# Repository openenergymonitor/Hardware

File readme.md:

## OpenEnergyMonitor Hardware

OpenEnergyMonitor hardware is open source hardware. This github repository hosts all the Eagle schematic and board files for the hardware units in addition to images for quick access.

**Update: most hardware designs have now been moved to dedicated repos, see individual folders**

### EmonTx

- [emonTx SMT V3](emonTxV3) - Latest generation of the emonTx Arduino compatible low power wireless energy monitoring node
- [emonTx Through-hole V2](emonTxV2) - A low-power wireless energy-monitoring node - Arduino compatible

### EmonTx Shield

- [emonTx Shield SMT](emontx-shield-smt) - An Arduino compatible energy monitoring shield
- [emonTx Shield Through-hole](emontx-shield-v1) - A wireless energy monitoring Arduino compatible shield

### EmonTH

- [emonTH](emonTH) - Temperature and humidity monitoring node

### EmonGLCD

- [emonGLCD](emonGLCD_V1) - Wireless open-source graphical LCD display unit - Arduino compatible

### RF12Pi Adapter Board

- [RF12Pi Adapter Board](RFM2Pi/readme.md)

### Development

- [12 Input Pulse Counter](12-input-pulse-counter) - Design in development for a 12-input puse counter for interfacing with 12 utility meters. 12 Input Pulse counter development notes and documentation can be found on the main OpenEnergyMonitor site [here](http://openenergymonitor.org/emon/buildingblocks/12-input-pulse-counting)

- [In-line energy monitor + Relay unit](relay-unit/readme.md)

### Open Hardware

Hardware designs (schematics and CAD) files are licensed under the [Creative Commons Attribution-ShareAlike 3.0 Unported License](http://creativecommons.org/licenses/by-sa/3.0/) and follow the terms of the [OSHW (Open-source hardware) Statement of Principles 1.0.](http://freedomdefined.org/OSHW)

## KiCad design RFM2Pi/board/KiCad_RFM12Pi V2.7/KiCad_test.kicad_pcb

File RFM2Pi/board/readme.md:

## moved to https://github.com/openenergymonitor/RFM2Pi

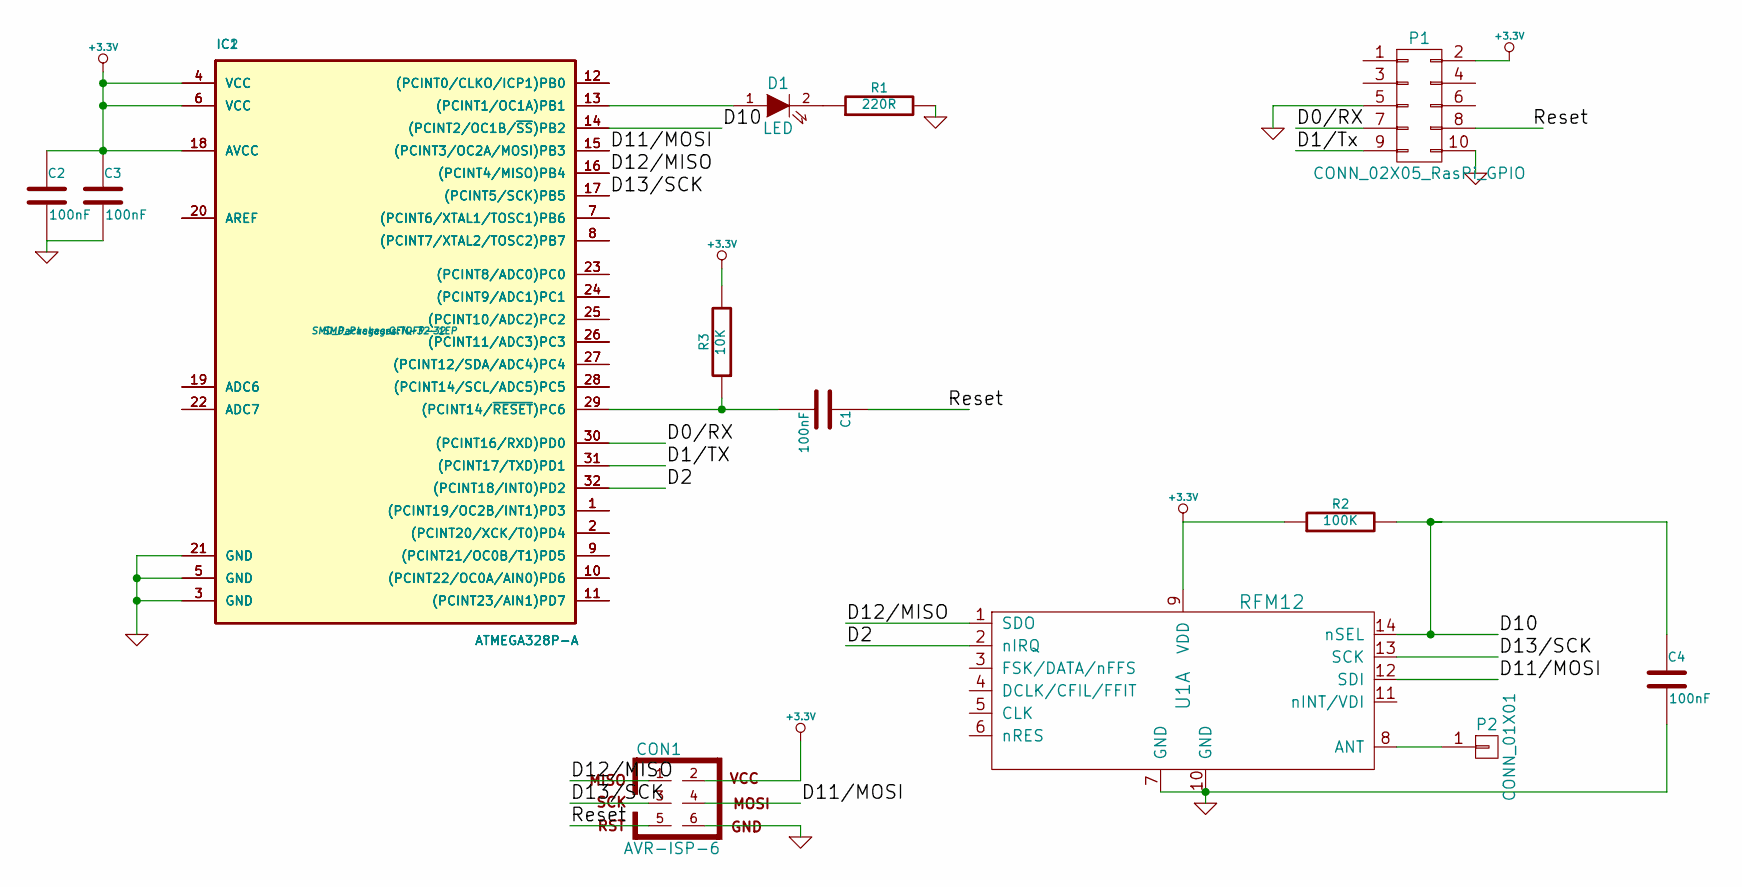
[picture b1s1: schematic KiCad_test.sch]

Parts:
C1, C2, C3, C4: 100nF; SMD-0603_c
CON1: AVR-ISP-6; Pin_Header_Straight_2x03
D1: LED; LED-0603
IC1: ATMEGA328P-A; TQFP-32
IC2: ATMEGA328P-A; QFN-32-1EP
P1: CONN_02X05_RasPi_GPIO; Pin_Header_Straight_2x05
P2: CONN_01X01; PINTST
R1: 220R; SMD-0603
R2: 100K; SMD-0603
R3: 10K; SMD-0603
U1: RFM12

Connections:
+3.3V: C2.1, C3.1, CON1.2, IC1.4 (VCC), IC1.6 (VCC), IC1.18 (AVCC), IC2.4 (VCC), IC2.6 (VCC), IC2.18 (AVCC), P1.2, R2.1, R3.2, U1.9 (VDD)
/D0/RX: IC1.30 ((PCINT16/RXD)PD0), IC2.30 ((PCINT16/RXD)PD0), P1.7
/D1/TX: IC1.31 ((PCINT17/TXD)PD1), IC2.31 ((PCINT17/TXD)PD1), P1.9
/D2: IC1.32 ((PCINT18/INT0)PD2), IC2.32 ((PCINT18/INT0)PD2), U1.2 (nIRQ)
/D10: C4.1, IC1.14 ((PCINT2/OC1B/~SS~)PB2), IC2.14 ((PCINT2/OC1B/~SS~)PB2), R2.2, U1.14 (nSEL)
/D11/MOSI: CON1.4, IC1.15 ((PCINT3/OC2A/MOSI)PB3), IC2.15 ((PCINT3/OC2A/MOSI)PB3), U1.12 (SDI)
/D12/MISO: CON1.1, IC1.16 ((PCINT4/MISO)PB4), IC2.16 ((PCINT4/MISO)PB4), U1.1 (SDO)
/D13/SCK: CON1.3, IC1.17 ((PCINT5/SCK)PB5), IC2.17 ((PCINT5/SCK)PB5), U1.13 (SCK)
/Reset: C1.1, CON1.5, P1.8
GND: C2.2, C3.2, C4.2, CON1.6, IC1.3 (GND), IC1.5 (GND), IC1.21 (GND), IC2.3 (GND), IC2.5 (GND), IC2.21 (GND), P1.5, P1.10, R1.2, U1.7 (GND), U1.10 (GND)
unnamed: C1.2, IC1.29 ((PCINT14/~RESET~)PC6), IC2.29 ((PCINT14/~RESET~)PC6), R3.1
unnamed: D1.1 (A), IC1.13 ((PCINT1/OC1A)PB1), IC2.13 ((PCINT1/OC1A)PB1)
unnamed: D1.2 (K), R1.1
unnamed: IC1.1 ((PCINT19/OC2B/INT1)PD3), IC2.1 ((PCINT19/OC2B/INT1)PD3)
unnamed: IC1.2 ((PCINT20/XCK/T0)PD4), IC2.2 ((PCINT20/XCK/T0)PD4)
unnamed: IC1.7 ((PCINT6/XTAL1/TOSC1)PB6), IC2.7 ((PCINT6/XTAL1/TOSC1)PB6)
unnamed: IC1.8 ((PCINT7/XTAL2/TOSC2)PB7), IC2.8 ((PCINT7/XTAL2/TOSC2)PB7)
unnamed: IC1.9 ((PCINT21/OC0B/T1)PD5), IC2.9 ((PCINT21/OC0B/T1)PD5)
unnamed: IC1.10 ((PCINT22/OC0A/AIN0)PD6), IC2.10 ((PCINT22/OC0A/AIN0)PD6)
unnamed: IC1.11 ((PCINT23/AIN1)PD7), IC2.11 ((PCINT23/AIN1)PD7)
unnamed: IC1.12 ((PCINT0/CLKO/ICP1)PB0), IC2.12 ((PCINT0/CLKO/ICP1)PB0)
unnamed: IC1.19 (ADC6), IC2.19 (ADC6)
unnamed: IC1.20 (AREF), IC2.20 (AREF)
unnamed: IC1.22 (ADC7), IC2.22 (ADC7)
unnamed: IC1.23 ((PCINT8/ADC0)PC0), IC2.23 ((PCINT8/ADC0)PC0)
unnamed: IC1.24 ((PCINT9/ADC1)PC1), IC2.24 ((PCINT9/ADC1)PC1)
unnamed: IC1.25 ((PCINT10/ADC2)PC2), IC2.25 ((PCINT10/ADC2)PC2)
unnamed: IC1.26 ((PCINT11/ADC3)PC3), IC2.26 ((PCINT11/ADC3)PC3)
unnamed: IC1.27 ((PCINT12/SDA/ADC4)PC4), IC2.27 ((PCINT12/SDA/ADC4)PC4)
unnamed: IC1.28 ((PCINT14/SCL/ADC5)PC5), IC2.28 ((PCINT14/SCL/ADC5)PC5)
unnamed: P2.1, U1.8 (ANT)

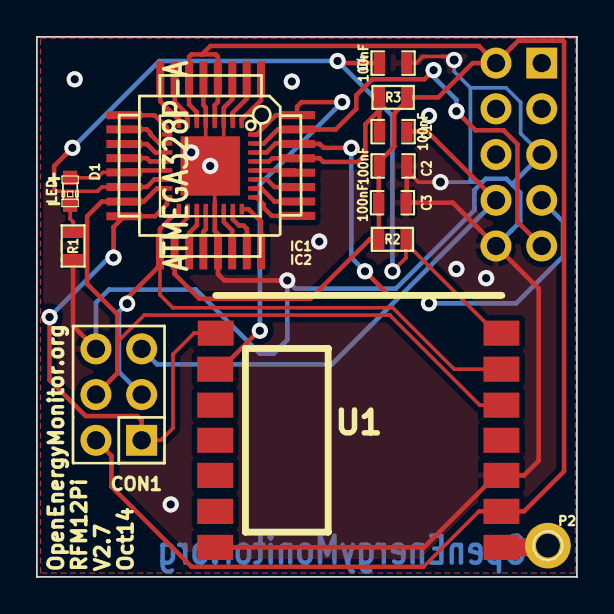
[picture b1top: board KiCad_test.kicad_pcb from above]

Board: 2 copper layers, 30.0 x 30.0 mm, 14 parts (1 on the bottom side), 31 nets.

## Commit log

2014-08-20 Initial readme
2014-08-20 formatting
2014-08-20 12 input pulse counter files
2014-08-20 EmonTx Shield SMT
2014-08-20 in development energy monitor + relay unit
2014-08-20 RFM2Pi schmatic and board image
2014-08-21 add emonTx, emonGLCD designs
2014-08-21 add new emonGLCD V1.5
2014-08-21 EmonTH and EmonTx shield v1 files
2014-08-21 open hardware logo
2014-08-21 IETSockets and CT image
2014-09-03 Development helpers
2014-09-03 Throughhole Atmega + RFM69 base example
2014-09-03 Rename
2014-09-03 Initial concept of updated through-hole emontx with powered by ACAC + 2 CT's fitting in EmonTH case.
2014-09-03 readme for emontx through-hole concept
2014-09-03 Updated relay-unit with atmega328 and rfm12/69
2014-09-03 New relay-unit design and old designs archived
2014-09-04 Single voltage regulator, power supply test results, usb positioning
2014-10-27 add RFM12Pi hardware
2014-10-27 edit rfm12pi readme
2014-10-27 edit readme
2014-10-29 RFM12Pi V2.7 revision compleate using kicad
2014-10-31 add rfm12pi v2.7 bom
2014-11-07 fix rfm12pi v2.6
2014-11-13 update kicad and remove rfm12ppi frmware, see openenergymonitor/rfm12pi repo for latest firmware
2014-12-08 add emonTx V3.4 files
2014-12-08 organise folders
2014-12-08 add readme for root folder
2015-02-06 add RFM12Pi V3.1
2015-02-06 add V3.1 readme
2015-02-06 update readme wth v3.1 images
2015-02-06 typo
2015-02-09 photos
2015-02-10 Add Ken credit
2015-02-28 add emonTx V3.4 BOM
2015-03-16 add emonPi and new emonTH
2015-04-28 add emonPi case CAD drawing with dimentions
2015-04-28 add .png drawing cad
2015-05-22 emontx throughhole 2
2015-06-01 Embodied energy analysis for the emonpi 1st draft
2015-06-06 EmonTx v2.5 design
2015-07-25 add emonPi V1.6
2015-11-24 add emonPi V1.6 board assembled photo
2015-11-24 resize photo
2015-11-26 add low res photo
2015-12-18 Heatpump Monitor hardware schematic and board file
2016-03-07 Introduce set of gitignore rules
    Combined together
    Eagle specific https://github.com/github/gitignore/blob/master/Eagle.gitignore
    and OSX specific https://github.com/github/gitignore/blob/master/Global/OSX.gitignore
2016-03-07 Removed backup copy of readmy.md files
2016-03-18 add emonTx V3.4.1 design
2016-07-27 emonTH V2.0 prototype
2016-07-28 add emonth v2.0.1 led footprint update
2016-08-19 emonTH gerbers
2016-08-19 add emonTx V3.4.2 & change log
2016-08-19 readme
2016-08-19 add export
2017-01-14 move emonglcd hardware to emonglcd repo
2017-02-27 update docs URL
2017-03-10 move hardware to dedicated repos
2019-01-21 https://github.com/decentralizedbloodbank/OpenLog
    https://github.com/decentralizedbloodbank/OpenLog
